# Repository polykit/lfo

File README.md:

# LFO

This repository contains schematics and PCB layout for a LFO with pulse and triangle output. There are rate, level and offset controls on the board. I used this in the [Polykit-6 built](https://www.youtube.com/watch?v=vj-DSh6yfM0&t=424s) to control frequency cutoff, resonance and pulse width.

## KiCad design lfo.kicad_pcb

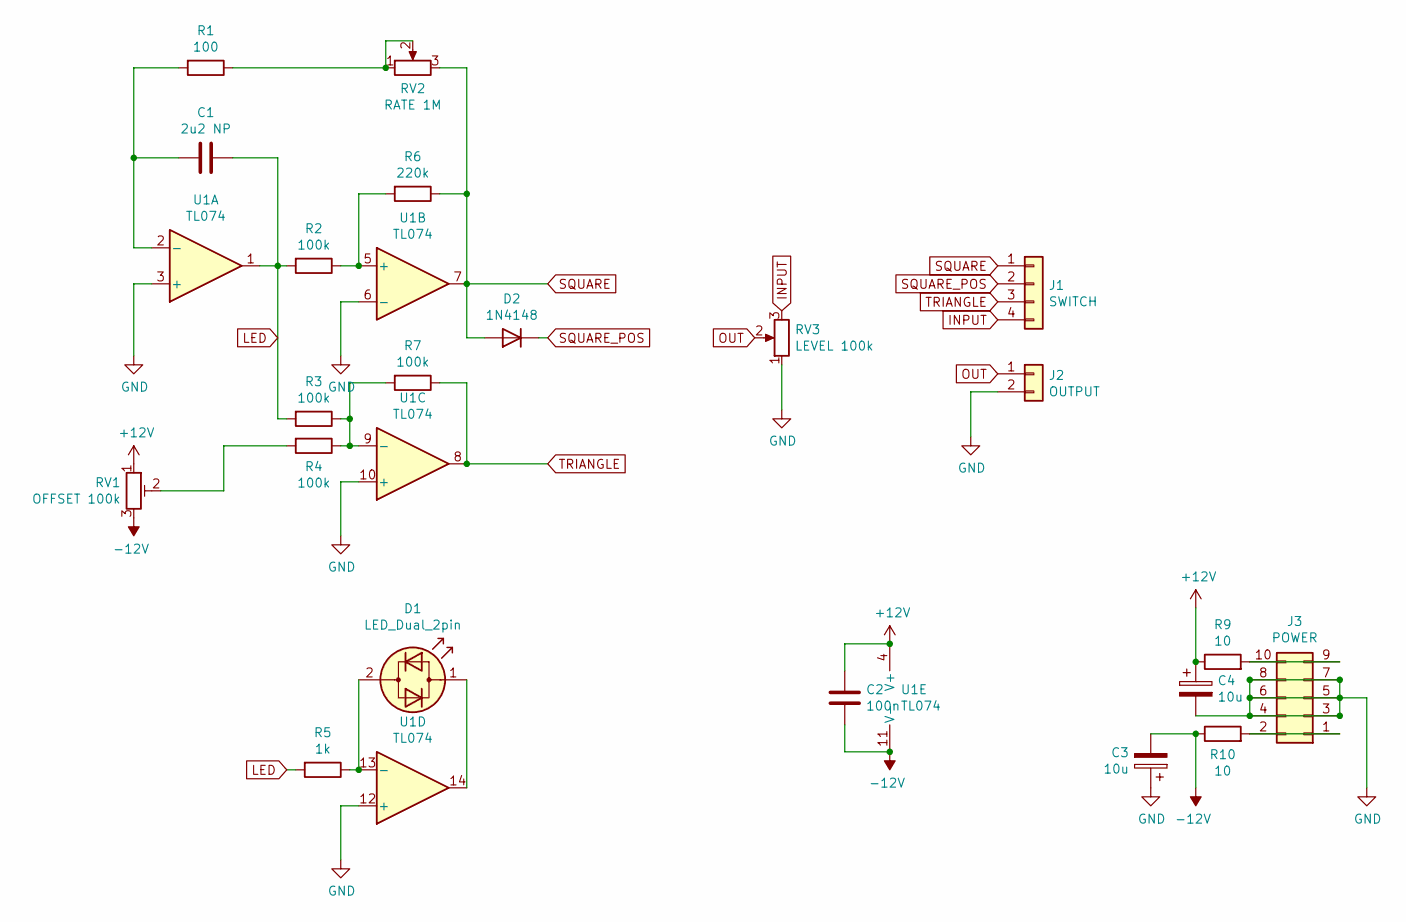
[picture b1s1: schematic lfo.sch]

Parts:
C1: 2u2 NP; C_Rect_L7.0mm_W3.5mm_P5.00mm
C2: 100n; C_Disc_D3.0mm_W2.0mm_P2.50mm
C3, C4: 10u; CP_Radial_D5.0mm_P2.50mm
D1: LED_Dual_2pin; LED_D5.0mm
D2: 1N4148; D_DO-35_SOD27_P7.62mm_Horizontal
J1: SWITCH; Molex_KK-254_AE-6410-04A_1x04_P2.54mm_Vertical
J2: OUTPUT; Molex_KK-254_AE-6410-02A_1x02_P2.54mm_Vertical
J3: POWER; IDC-Header_2x05_P2.54mm_Vertical
R1: 100; R_Axial_DIN0207_L6.3mm_D2.5mm_P10.16mm_Horizontal
R2, R3, R4, R7: 100k; R_Axial_DIN0207_L6.3mm_D2.5mm_P10.16mm_Horizontal
R5: 1k; R_Axial_DIN0207_L6.3mm_D2.5mm_P10.16mm_Horizontal
R6: 220k; R_Axial_DIN0207_L6.3mm_D2.5mm_P10.16mm_Horizontal
R9, R10: 10; R_Axial_DIN0207_L6.3mm_D2.5mm_P10.16mm_Horizontal
RV1: OFFSET 100k; Potentiometer_ACP_CA9-H5_Horizontal
RV2: RATE 1M; Potentiometer_Alpha_RD901F-40-00D_Single_Vertical
RV3: LEVEL 100k; Potentiometer_Alpha_RD901F-40-00D_Single_Vertical
U1: TL074; DIP-14_W7.62mm_Socket_LongPads

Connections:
+12V: C2.1, C4.1, R9.1, RV1.1, U1.4 (V+)
-12V: C2.2, C3.2, R10.1, RV1.3, U1.11 (V-)
GND: C3.1, C4.2, J2.2, J3.3, J3.4, J3.5, J3.6, J3.7, J3.8, RV3.1, U1.3 (+), U1.6 (-), U1.10 (+), U1.12 (+)
INPUT: J1.4, RV3.3
LED: C1.1, R2.2, R3.2, R5.2, U1.1
unnamed: C1.2, R1.2, U1.2 (-)
unnamed: D1.1 (KA), U1.14
unnamed: D1.2 (AK), R5.1, U1.13 (-)
unnamed: J3.1, J3.2, R10.2
unnamed: J3.9, J3.10, R9.2
unnamed: R1.1, RV2.1, RV2.2
unnamed: R2.1, R6.2, U1.5 (+)
unnamed: R3.1, R4.1, R7.2, U1.9 (-)
unnamed: R4.2, RV1.2
OUT: J2.1, RV3.2
SQUARE: D2.2 (A), J1.1, R6.1, RV2.3, U1.7
SQUARE_POS: D2.1 (K), J1.2
TRIANGLE: J1.3, R7.1, U1.8

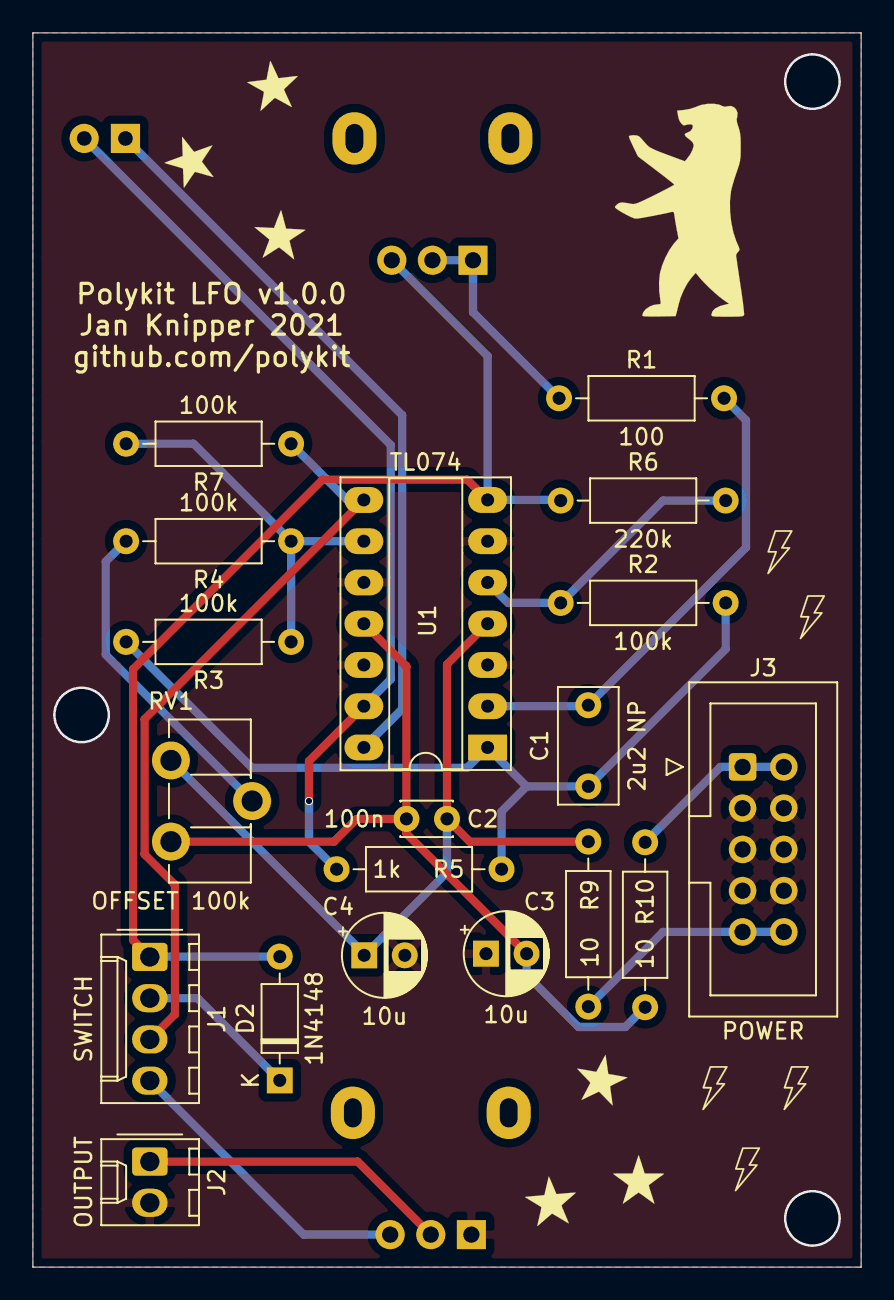
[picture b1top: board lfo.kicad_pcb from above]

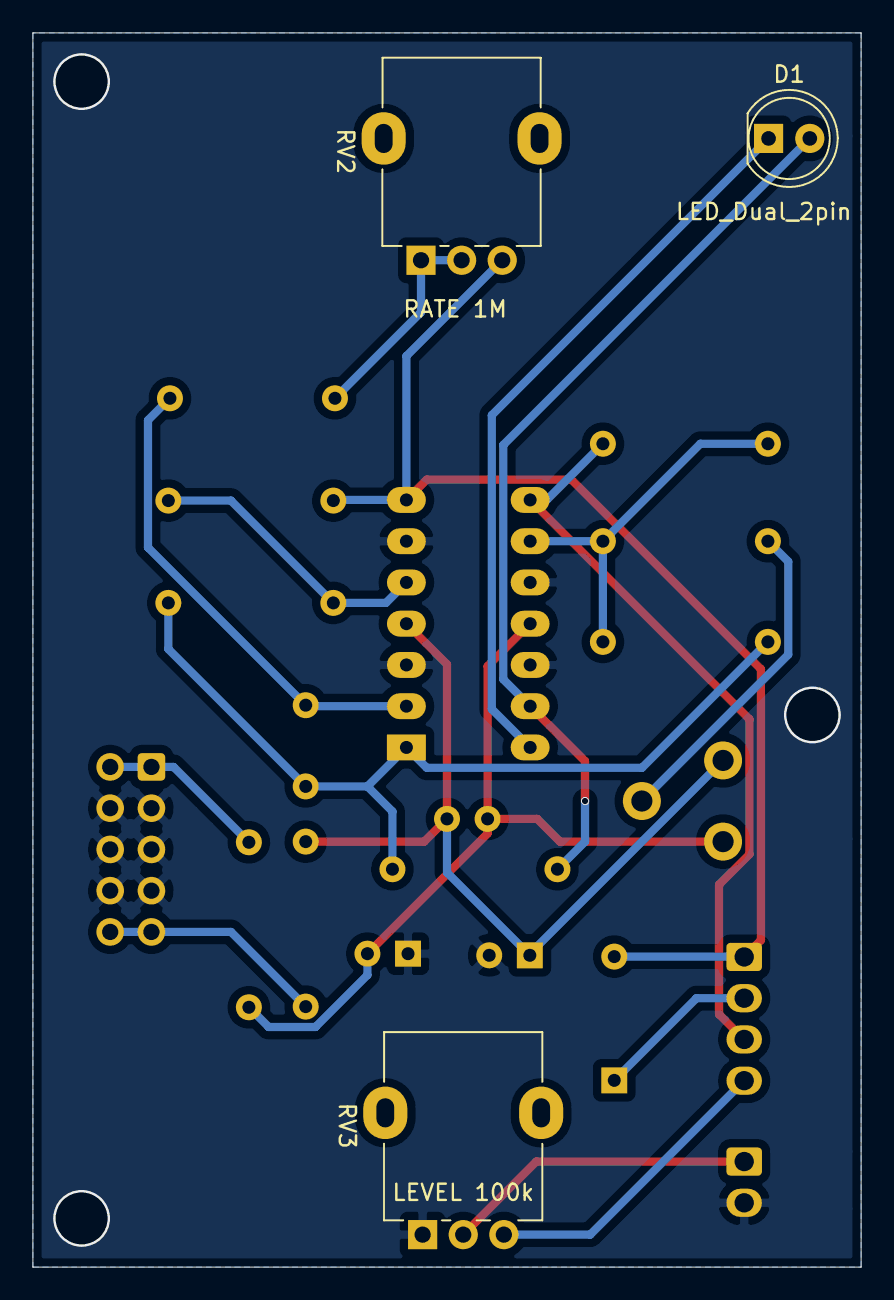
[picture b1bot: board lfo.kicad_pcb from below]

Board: 2 copper layers, 51.0 x 76.0 mm, 22 parts (3 on the bottom side), 18 nets.

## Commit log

2022-02-03 Initial import
2022-02-03 Remove backups
